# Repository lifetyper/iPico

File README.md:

# iPico
Open Hardware Secure Key Using Pico Fido Firmware

.

1.Using same gpio as raspi pico

2.Light guide using Φ2*2.54mm

3.Screw using M1*4mm

4.Keep USB footprint bottom side clean without too much solder

5.You might need to polish the outline of PCB if it's not done by the manufacture

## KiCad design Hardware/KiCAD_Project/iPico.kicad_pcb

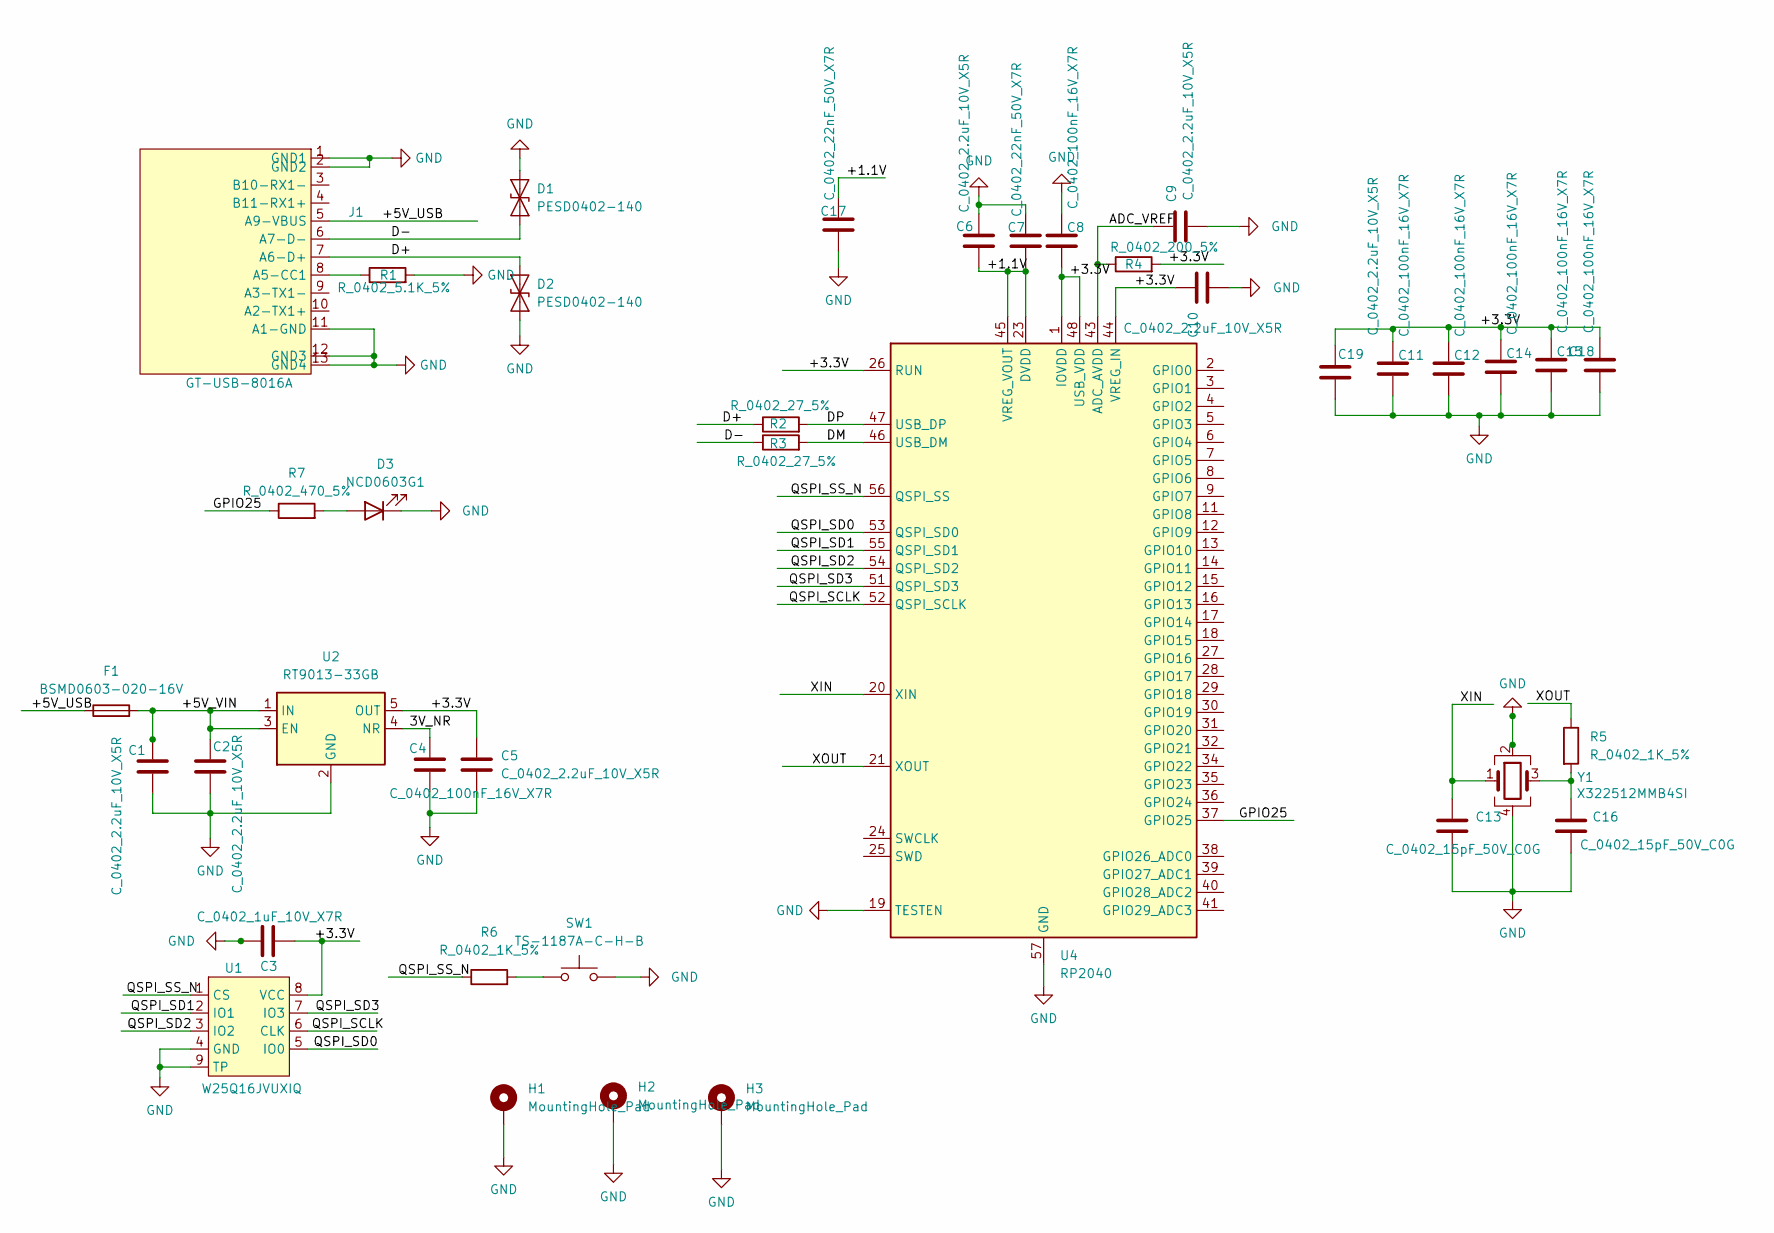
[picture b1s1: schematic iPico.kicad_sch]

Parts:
C1, C2, C5, C6, C9, C10, C19: C_0402_2.2uF_10V_X5R; C_0402_1005Metric
C3: C_0402_1uF_10V_X7R; C_0402_1005Metric
C4, C8, C11, C12, C14, C15, C18: C_0402_100nF_16V_X7R; C_0402_1005Metric
C7, C17: C_0402_22nF_50V_X7R; C_0402_1005Metric
C13, C16: C_0402_15pF_50V_C0G; C_0402_1005Metric
D1, D2: PESD0402-140; D_0402_1005Metric
D3: NCD0603G1; LED_0603_1608Metric
F1: BSMD0603-020-16V; Fuse_0603_1608Metric
H1, H2, H3: MountingHole_Pad; MountingHole-M1
J1: GT-USB-8016A
R1: R_0402_5.1K_5%; R_0402_1005Metric
R2, R3: R_0402_27_5%; R_0402_1005Metric
R4: R_0402_200_5%; R_0402_1005Metric
R5, R6: R_0402_1K_5%; R_0402_1005Metric
R7: R_0402_470_5%; R_0402_1005Metric
SW1: TS-1187A-C-H-B; SW_Push_1P1T_XKB_TS-1187A
U1: W25Q16JVUXIQ; USON8-2x3mm-EP0.2x1.6mm
U2: RT9013-33GB; SOT-23-5
U4: RP2040; QFN-56-1EP_7x7mm_P0.4mm_EP3.2x3.2mm
Y1: X322512MMB4SI; Crystal_SMD_2520-4Pin_2.5x2.0mm

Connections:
/3V_NR: C4.1, U2.4 (NR)
/+1.1V: C6.2, C7.2, C17.1, U4.23 (DVDD), U4.45 (VREG_VOUT), U4.50 (DVDD)
/+3.3V: C3.2, C5.1, C8.2, C10.1, C11.1, C12.1, C14.1, C15.1, C18.1, C19.2, R4.2, U1.8 (VCC), U2.5 (OUT), U4.1 (IOVDD), U4.10 (IOVDD), U4.22 (IOVDD), U4.26 (RUN), U4.33 (IOVDD), U4.42 (IOVDD), U4.44 (VREG_IN), U4.48 (USB_VDD), U4.49 (IOVDD)
/+5V_USB: F1.1, J1.5 (A9-VBUS)
/+5V_VIN: C1.1, C2.1, F1.2, U2.1 (IN), U2.3 (EN)
/ADC_VREF: C9.1, R4.1, U4.43 (ADC_AVDD)
/D+: D2.2 (A2), J1.7 (A6-D+), R2.1
/D-: D1.1 (A1), J1.6 (A7-D-), R3.1
/DM: R3.2, U4.46 (USB_DM)
/DP: R2.2, U4.47 (USB_DP)
/GPIO25: R7.1, U4.37 (GPIO25)
/QSPI_SCLK: U1.6 (CLK), U4.52 (QSPI_SCLK)
/QSPI_SD0: U1.5 (IO0), U4.53 (QSPI_SD0)
/QSPI_SD1: U1.2 (IO1), U4.55 (QSPI_SD1)
/QSPI_SD2: U1.3 (IO2), U4.54 (QSPI_SD2)
/QSPI_SD3: U1.7 (IO3), U4.51 (QSPI_SD3)
/QSPI_SS_N: R6.1, U1.1 (CS), U4.56 (QSPI_SS)
/XIN: C13.1, U4.20 (XIN), Y1.1
/XOUT: R5.1, U4.21 (XOUT)
GND: C1.2, C2.2, C3.1, C4.2, C5.2, C6.1, C7.1, C8.1, C9.2, C10.2, C11.2, C12.2, C13.2, C14.2, C15.2, C16.2, C17.2, C18.2, C19.1, D1.2 (A2), D2.1 (A1), D3.1 (K), H1.1, H2.1, H3.1, J1.1 (GND1), J1.2 (GND2), J1.11 (A1-GND), J1.12 (GND3), J1.13 (GND4), R1.2, SW1.2, U1.4 (GND), U1.9 (TP), U2.2 (GND), U4.19 (TESTEN), U4.57 (GND), Y1.2, Y1.4
unnamed: C16.1, R5.2, Y1.3
unnamed: D3.2 (A), R7.2
unnamed: J1.8 (A5-CC1), R1.1
unnamed: R6.2, SW1.1

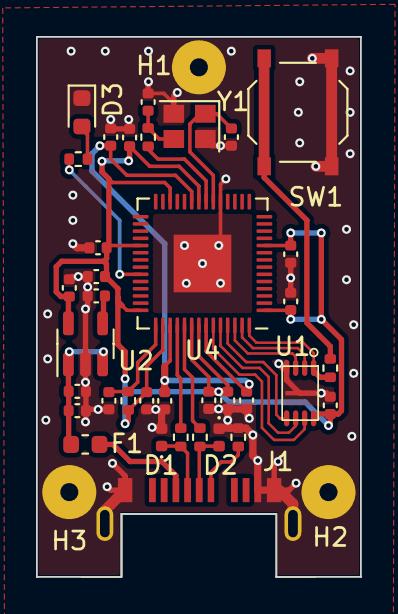
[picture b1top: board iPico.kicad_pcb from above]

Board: 2 copper layers, 18.0 x 30.0 mm, 39 parts (0 on the bottom side), 24 nets.

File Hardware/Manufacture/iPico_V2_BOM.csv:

#,Reference,Qty,Value,Footprint,DNP
1,"C1, C2, C5, C6, C9, C10, C19",7,C_0402_2.2uF_10V_X5R,Capacitor_SMD:C_0402_1005Metric,
2,C3,1,C_0402_1uF_10V_X7R,Capacitor_SMD:C_0402_1005Metric,
3,"C4, C8, C11, C12, C14, C15, C18",7,C_0402_100nF_16V_X7R,Capacitor_SMD:C_0402_1005Metric,
4,"C7, C17",2,C_0402_22nF_50V_X7R,Capacitor_SMD:C_0402_1005Metric,
5,"C13, C16",2,C_0402_15pF_50V_C0G,Capacitor_SMD:C_0402_1005Metric,
6,"D1, D2",2,PESD0402-140 ,Diode_SMD:D_0402_1005Metric,
7,D3,1,NCD0603G1,LED_SMD:LED_0603_1608Metric,
8,F1,1,BSMD0603-020-16V,Fuse:Fuse_0603_1608Metric,
9,"H1, H2, H3",3,MountingHole_Pad,TinyMountingHole:MountingHole-M1,
10,J1,1,GT-USB-8016A,GT-USB-8016A:GT-USB-8016A,
11,R1,1,R_0402_5.1K_5%,Resistor_SMD:R_0402_1005Metric,
12,"R2, R3",2,R_0402_27_5%,Resistor_SMD:R_0402_1005Metric,
13,R4,1,R_0402_200_5%,Resistor_SMD:R_0402_1005Metric,
14,"R5, R6",2,R_0402_1K_5%,Resistor_SMD:R_0402_1005Metric,
15,R7,1,R_0402_470_5%,Resistor_SMD:R_0402_1005Metric,
16,SW1,1,TS-1187A-C-H-B,SW_PUSH_1P1P_XKB_TS-1187A_W3D:SW_Push_1P1T_XKB_TS-1187A,
17,U1,1,W25Q16JVUXIQ,USON8:USON8-2x3mm-EP0.2x1.6mm,
18,U2,1,RT9013-33GB,Package_TO_SOT_SMD:SOT-23-5,
19,U4,1,RP2040,Package_DFN_QFN:QFN-56-1EP_7x7mm_P0.4mm_EP3.2x3.2mm,
20,Y1,1,X322512MMB4SI,Crystal:Crystal_SMD_2520-4Pin_2.5x2.0mm,

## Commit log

2023-12-25 Initial
2023-12-25 Add ReadMe
2023-12-29 Update README.md
    add photos
